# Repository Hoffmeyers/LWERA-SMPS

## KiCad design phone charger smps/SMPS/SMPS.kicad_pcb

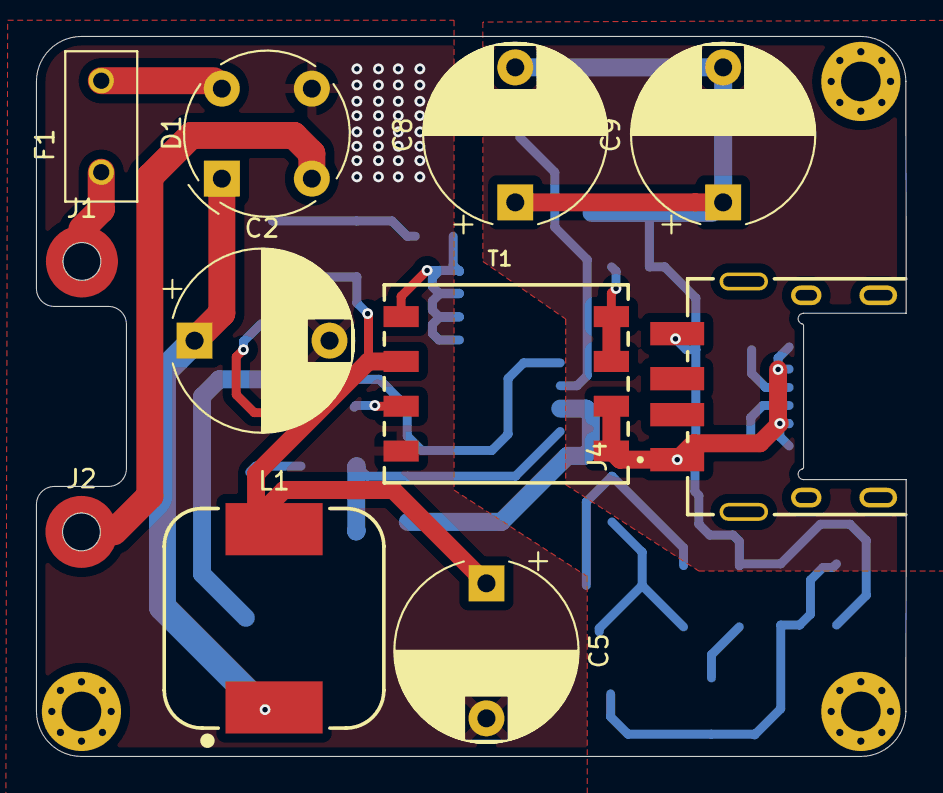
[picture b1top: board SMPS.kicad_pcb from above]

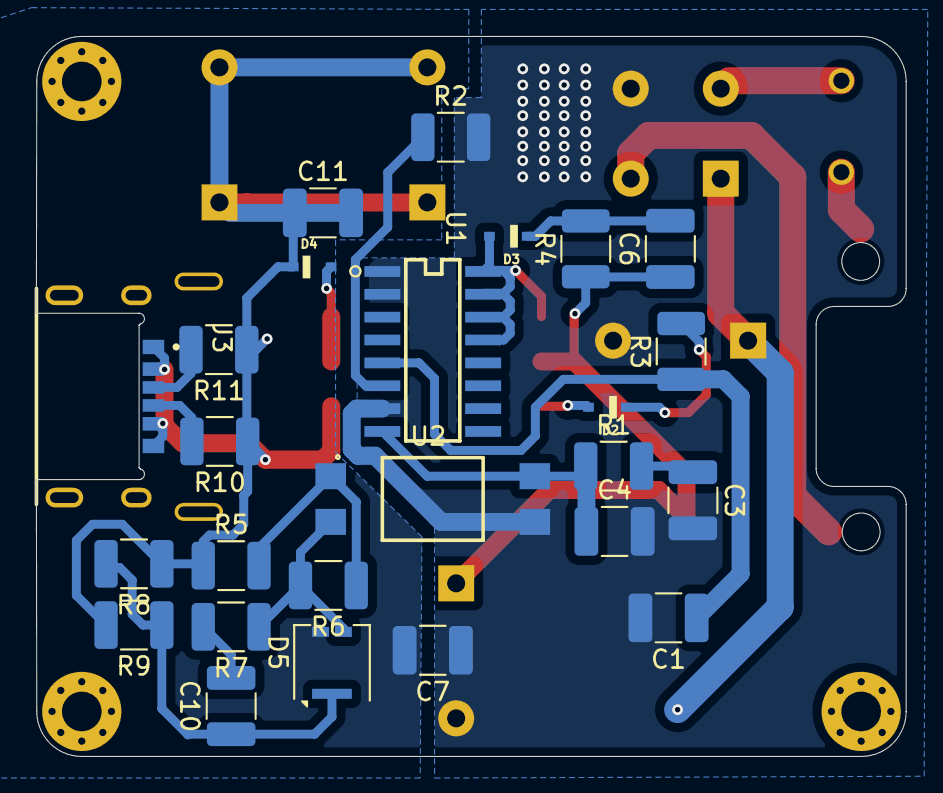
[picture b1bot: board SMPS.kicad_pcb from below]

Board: 2 copper layers, 48.3 x 40.0 mm, 36 parts (25 on the bottom side), 23 nets.

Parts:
C1, C6: 1nF; C_1210_3225Metric_Pad1.33x2.70mm_HandSolder
C2, C5: 12uF; CP_Radial_D10.0mm_P7.50mm
C3: 330nF; C_1210_3225Metric_Pad1.33x2.70mm_HandSolder
C4: 220pF; C_1210_3225Metric_Pad1.33x2.70mm_HandSolder
C7: C; C_1210_3225Metric_Pad1.33x2.70mm_HandSolder
C8, C9: 560uF; CP_Radial_D10.0mm_P7.50mm
C10: 12nF; C_1210_3225Metric_Pad1.33x2.70mm_HandSolder
C11: 1uF; C_1210_3225Metric_Pad1.33x2.70mm_HandSolder
D1: RB157; Diode_Bridge_Round_D9.0mm
D2, D3, D4: 1N4148WSQ-7-F; SOD2513X120N
D5: D_Schottky_Dual_Series_CAK; Littelfuse_PolyZen-LS
F1: RSTA-2.5-BULK; FUSE_RST-1-BULK
J1, J2: Screw_Terminal_01x01; Mounting_Wuerth_WA-SMSI-M1.6_H1mm_9774010633
J3: USB4515-GF-A_REVA; GCT_USB4515-GF-A_REVA
J4: USB1046-GF-0190-L-B-A_REVB4; GCT_USB1046-GF-0190-L-B-A_REVB4
L1: WE-PD_1210
R1: 3.3K; R_1210_3225Metric_Pad1.30x2.65mm_HandSolder
R2: R; R_1210_3225Metric_Pad1.30x2.65mm_HandSolder
R3: 33; R_1210_3225Metric_Pad1.30x2.65mm_HandSolder
R4: 220k; R_1210_3225Metric_Pad1.30x2.65mm_HandSolder
R5: 100; R_1210_3225Metric_Pad1.30x2.65mm_HandSolder
R6: 12k; R_1210_3225Metric_Pad1.30x2.65mm_HandSolder
R7: 1M; R_1210_3225Metric_Pad1.30x2.65mm_HandSolder
R8: 130K; R_1210_3225Metric_Pad1.30x2.65mm_HandSolder
R9: 43K; R_1210_3225Metric_Pad1.30x2.65mm_HandSolder
R10, R11: 10k; R_1210_3225Metric_Pad1.30x2.65mm_HandSolder
T1: WE-FB_EP7_SCH1; WE-FB_EP7_P11.68
U1: VIPER26LD; SO16N
U2: VO617A-3X018T; SOIC254P1210X390-4N

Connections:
GND1: C1.2, C2.2, C3.2, C4.2, C5.2, C7.1, D1.3 (-), R2.2, T1.1, U1.1 (GND), U1.2 (GND), U1.7 (FB), U2.3
GND2: C7.2, C8.2, C9.2, C11.2, D5.2 (A), J3.A12 (GND), J3.B12 (GND), J4.4 (GND), R9.2, T1.7, T1.8
unnamed: C3.1, R1.2
unnamed: C5.1, C6.1, L1.2, R4.1, T1.3
unnamed: C6.2, D3.C, R4.2
unnamed: C10.2, R7.2
unnamed: C2.1, D1.1 (+), L1.1
unnamed: D1.4, F1.2
unnamed: D2.A, T1.2
unnamed: D2.C, R3.2
unnamed: D3.A, T1.4, U1.13 (DRAIN), U1.14 (DRAIN), U1.15 (DRAIN), U1.16 (DRAIN)
unnamed: D4.A, T1.5, T1.6
unnamed: D5.3 (K), R6.2, R7.1, U2.2
unnamed: C10.1, D5.1 (common), R8.2, R9.1
unnamed: F1.1, J1.1
unnamed: D1.2, J2.1
unnamed: J3.A5 (CC1), R11.2
unnamed: J3.B5 (CC2), R10.2
unnamed: C8.1, C9.1, C11.1, D4.C, J3.A9 (VBUS), J3.B9 (VBUS), J4.1 (VCC), R5.1, R8.1, R10.1, R11.1
unnamed: R5.2, R6.1, U2.1
unnamed: C4.1, R1.1, U1.8 (COMP), U2.4
unnamed: R2.1, U1.6 (LIM)
unnamed: C1.1, R3.1, U1.5 (VDD)

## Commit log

2025-10-01 commit one
